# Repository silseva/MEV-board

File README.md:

# MEV board

Design files of the controller board used in the proof-of-concept setup of the [Multiple Emergency Ventilator project](https://mev.deib.polimi.it/).

The board has been designed to be coupled with an STM32F429 discovery board from ST Microelectronics (STM32F429I-DISC1) and serves a double puropose:
* controller for the closed-loop system regulating the bell-jar level;
* controller for the inspiration/expiration valves at bed side.

The design files are released in the Kicad 8.0 format under the [Creative Commons BY-NC-SA 4.0 license](https://creativecommons.org/licenses/by-nc-sa/4.0/).

**DISCLAIMER:** the hardware design made available in this repository has been made for a proof-of-concept setup. Therefore, it must not be considered safe for clinical use.

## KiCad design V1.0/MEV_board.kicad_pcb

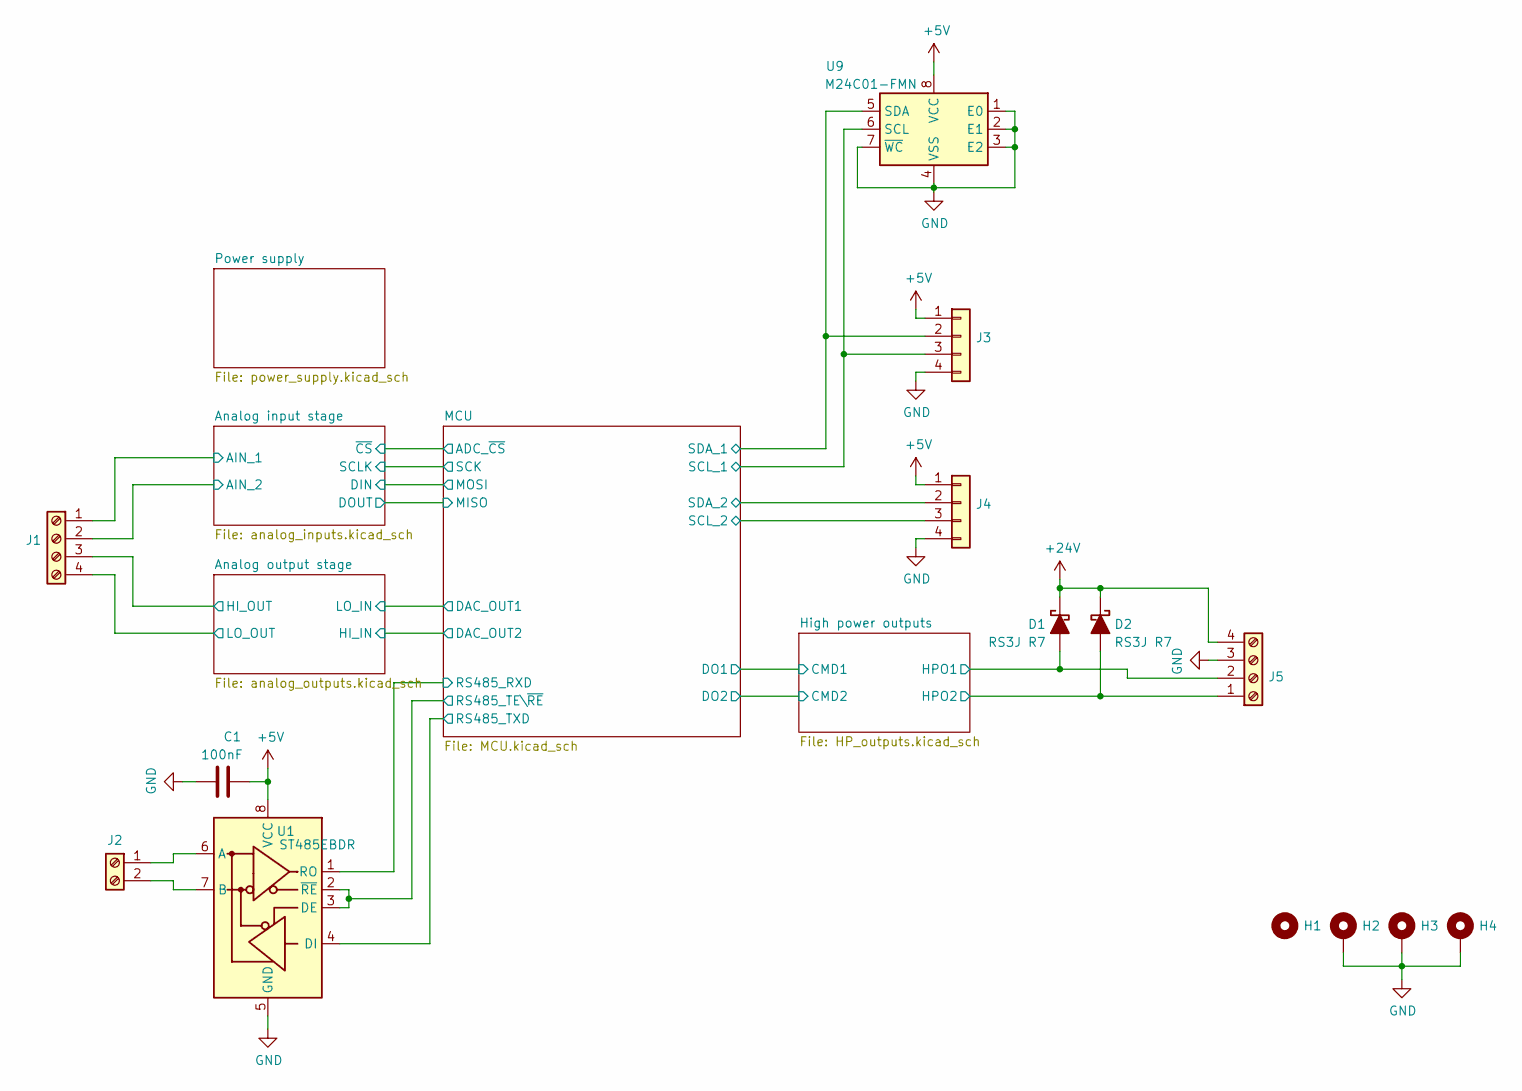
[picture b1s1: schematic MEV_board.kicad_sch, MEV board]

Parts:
C1: 100nF; C_0603_1608Metric_Pad1.08x0.95mm_HandSolder
D1, D2: RS3J R7; D_SMC_Handsoldering
H1, H2, H3, H4: MountingHole_3.2mm_M3_Pad_TopBottom
J1, J5: TerminalBlock_Phoenix_MKDS-1,5-4-5.08_1x04_P5.08mm_Horizont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
J2: TerminalBlock_Phoenix_MKDS-1,5-2-5.08_1x02_P5.08mm_Horizont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
J3, J4: PinHeader_1x04_P2.54mm_Vertical
U1: ST485EBDR; SOIC-8_3.9x4.9mm_P1.27mm
U9: M24C01-FMN; SOIC-8_3.9x4.9mm_P1.27mm

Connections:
+5V: C1.1, J3.1, J4.1, U1.8 (VCC), U9.8 (VCC); also elsewhere on the board
+24V: D1.1 (K), D2.1 (K), J5.4; also elsewhere on the board
/Analog input stage/AIN_1: J1.1; also elsewhere on the board
/Analog input stage/AIN_2: J1.2; also elsewhere on the board
/Analog output stage/HI_OUT: J1.3; also elsewhere on the board
/Analog output stage/LO_OUT: J1.4; also elsewhere on the board
/High power outputs/HPO1: D1.2 (A), J5.2; also elsewhere on the board
/High power outputs/HPO2: D2.2 (A), J5.1; also elsewhere on the board
/MCU/RS485_RXD: U1.1 (RO); also elsewhere on the board
/MCU/RS485_TE\~RE: U1.2 (~RE), U1.3 (DE); also elsewhere on the board
/MCU/RS485_TXD: U1.4 (DI); also elsewhere on the board
/MCU/SCL_1: J3.3, U9.6 (SCL); also elsewhere on the board
/MCU/SCL_2: J4.3; also elsewhere on the board
/MCU/SDA_1: J3.2, U9.5 (SDA); also elsewhere on the board
/MCU/SDA_2: J4.2; also elsewhere on the board
GND: C1.2, H2.1, H3.1, H4.1, J3.4, J4.4, J5.3, U1.5 (GND), U9.1 (E0), U9.2 (E1), U9.3 (E2), U9.4 (VSS), U9.7 (~WC); also elsewhere on the board

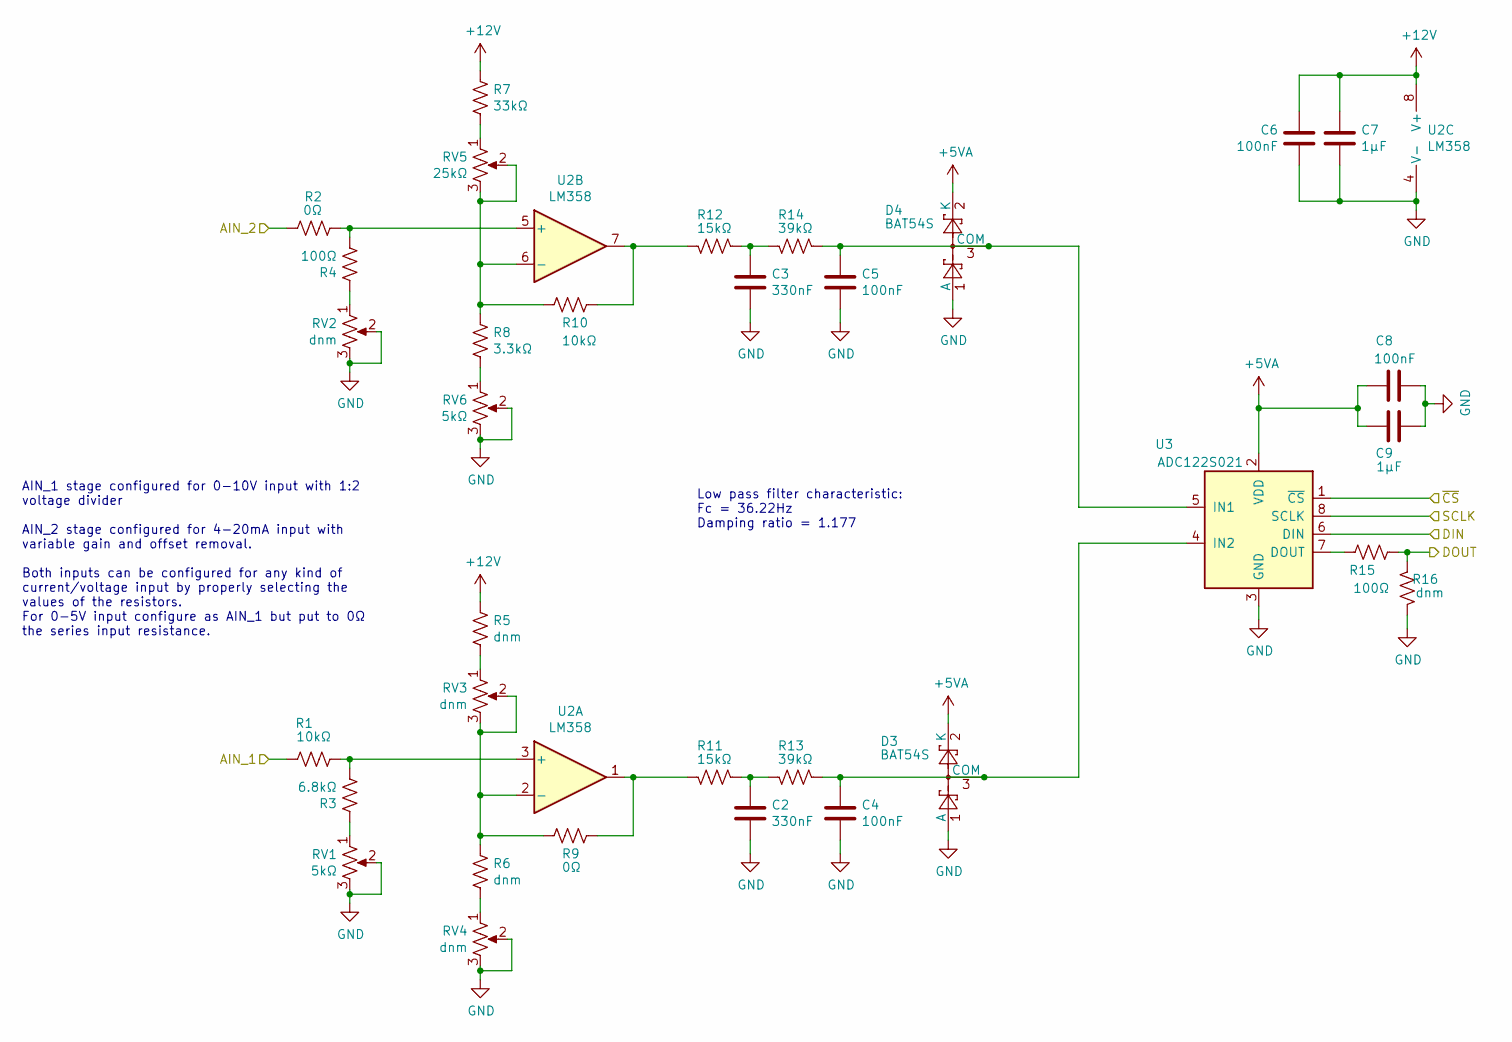
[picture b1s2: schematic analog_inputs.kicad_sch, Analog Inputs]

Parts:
C2, C3: 330nF; C_0805_2012Metric_Pad1.18x1.45mm_HandSolder
C4, C5: 100nF; C_0805_2012Metric_Pad1.18x1.45mm_HandSolder
C6, C8: 100nF; C_0603_1608Metric_Pad1.08x0.95mm_HandSolder
C7, C9: 1μF; C_0603_1608Metric_Pad1.08x0.95mm_HandSolder
D3, D4: BAT54S; SOT-23
R1, R10: 10kΩ; R_0805_2012Metric_Pad1.20x1.40mm_HandSolder
R2, R9: 0Ω; R_0805_2012Metric_Pad1.20x1.40mm_HandSolder
R3: 6.8kΩ; R_0805_2012Metric_Pad1.20x1.40mm_HandSolder
R4: 100Ω; R_0805_2012Metric_Pad1.20x1.40mm_HandSolder
R5, R6, R16: dnm; R_0805_2012Metric_Pad1.20x1.40mm_HandSolder
R7: 33kΩ; R_0805_2012Metric_Pad1.20x1.40mm_HandSolder
R8: 3.3kΩ; R_0805_2012Metric_Pad1.20x1.40mm_HandSolder
R11, R12: 15kΩ; R_0603_1608Metric_Pad0.98x0.95mm_HandSolder
R13, R14: 39kΩ; R_0603_1608Metric_Pad0.98x0.95mm_HandSolder
R15: 100Ω; R_0603_1608Metric_Pad0.98x0.95mm_HandSolder
RV1, RV6: 5kΩ; Potentiometer_Bourns_3296W_Vertical
RV2, RV3, RV4: dnm; Potentiometer_Bourns_3296W_Vertical
RV5: 25kΩ; Potentiometer_Bourns_3296W_Vertical
U2: LM358; SOIC-8_3.9x4.9mm_P1.27mm
U3: ADC122S021; VSSOP-8_3.0x3.0mm_P0.65mm

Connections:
+5VA: C8.1, C9.1, D3.2 (K), D4.2 (K), U3.2 (VDD); also elsewhere on the board
+12V: C6.2, C7.1, R5.1, R7.1, U2.8 (V+); also elsewhere on the board
/Analog input stage/AIN_1: R1.1; also elsewhere on the board
/Analog input stage/AIN_2: R2.1; also elsewhere on the board
/Analog input stage/DIN: U3.6 (DIN); also elsewhere on the board
/Analog input stage/DOUT: R15.2, R16.1; also elsewhere on the board
/MCU/ADC_~CS: U3.1 (~CS); also elsewhere on the board
/MCU/SCK: U3.8 (SCLK); also elsewhere on the board
GND: C2.2, C3.2, C4.2, C5.2, C6.1, C7.2, C8.2, C9.2, D3.1 (A), D4.1 (A), R16.2, RV1.2, RV1.3, RV2.2, RV2.3, RV4.2, RV4.3, RV6.2, RV6.3, U2.4 (V-), U3.3 (GND); also elsewhere on the board
unnamed: C2.1, R11.1, R13.2
unnamed: C3.1, R12.1, R14.2
unnamed: C4.1, D3.3 (COM), R13.1, U3.4 (IN2)
unnamed: C5.1, D4.3 (COM), R14.1, U3.5 (IN1)
unnamed: R1.2, R3.2, U2.3 (+)
unnamed: R2.2, R4.2, U2.5 (+)
unnamed: R3.1, RV1.1
unnamed: R4.1, RV2.1
unnamed: R5.2, RV3.1
unnamed: R6.1, R9.2, RV3.2, RV3.3, U2.2 (-)
unnamed: R6.2, RV4.1
unnamed: R7.2, RV5.1
unnamed: R8.2, RV6.1
unnamed: R10.1, R12.2, U2.7
unnamed: R8.1, R10.2, RV5.2, RV5.3, U2.6 (-)
unnamed: R9.1, R11.2, U2.1
unnamed: R15.1, U3.7 (DOUT)

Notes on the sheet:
AIN_1 stage configured for 0-10V input with 1:2 voltage divider AIN_2 stage configured for 4-20mA input with variable gain and offset removal. Both inputs can be configured for any kind of current/voltage input by properly selecting the values of the resistors. For 0-5V input configure as AIN_1 but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
Low pass filter characteristic: Fc = 36.22Hz Damping ratio = 1.177

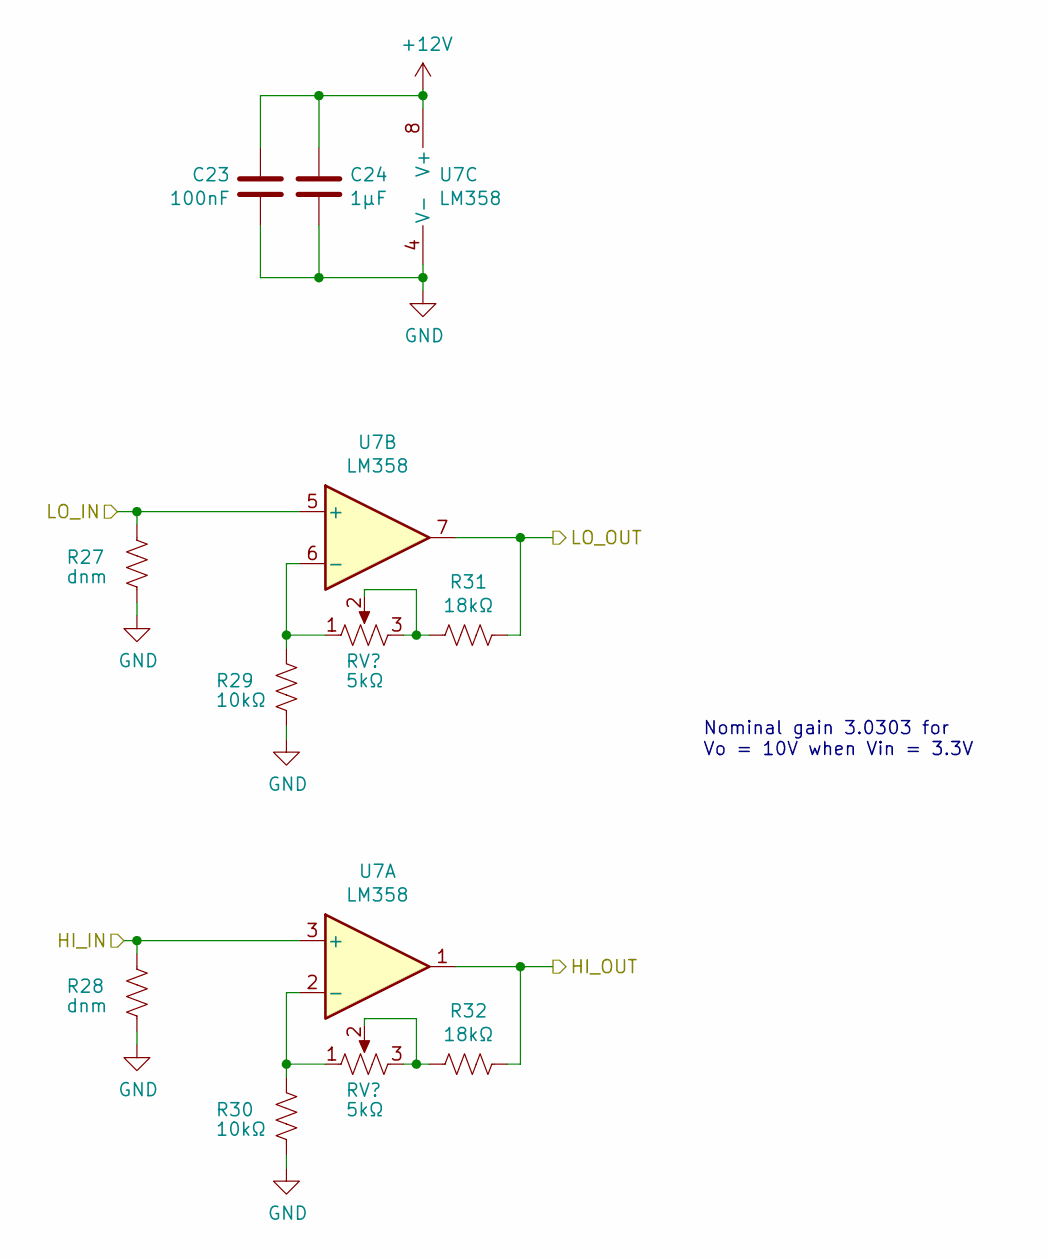
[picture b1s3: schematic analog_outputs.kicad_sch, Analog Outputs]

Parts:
C23: 100nF; C_0603_1608Metric_Pad1.08x0.95mm_HandSolder
C24: 1μF; C_0603_1608Metric_Pad1.08x0.95mm_HandSolder
R27, R28: dnm; R_0805_2012Metric_Pad1.20x1.40mm_HandSolder
R29, R30: 10kΩ; R_0805_2012Metric_Pad1.20x1.40mm_HandSolder
R31, R32: 18kΩ; R_0805_2012Metric_Pad1.20x1.40mm_HandSolder
RV7, RV8: 5kΩ; Potentiometer_Bourns_3296W_Vertical
U7: LM358; SOIC-8_3.9x4.9mm_P1.27mm

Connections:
+12V: C23.2, C24.1, U7.8 (V+); also elsewhere on the board
/Analog output stage/HI_OUT: R32.1, U7.1; also elsewhere on the board
/Analog output stage/LO_OUT: R31.1, U7.7; also elsewhere on the board
/MCU/DAC_OUT1: R27.1, U7.5 (+); also elsewhere on the board
/MCU/DAC_OUT2: R28.1, U7.3 (+); also elsewhere on the board
GND: C23.1, C24.2, R27.2, R28.2, R29.2, R30.2, U7.4 (V-); also elsewhere on the board
unnamed: R29.1, RV7.1, U7.6 (-)
unnamed: R30.1, RV8.1, U7.2 (-)
unnamed: R31.2, RV7.2, RV7.3
unnamed: R32.2, RV8.2, RV8.3

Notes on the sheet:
Nominal gain 3.0303 for Vo = 10V when Vin = 3.3V

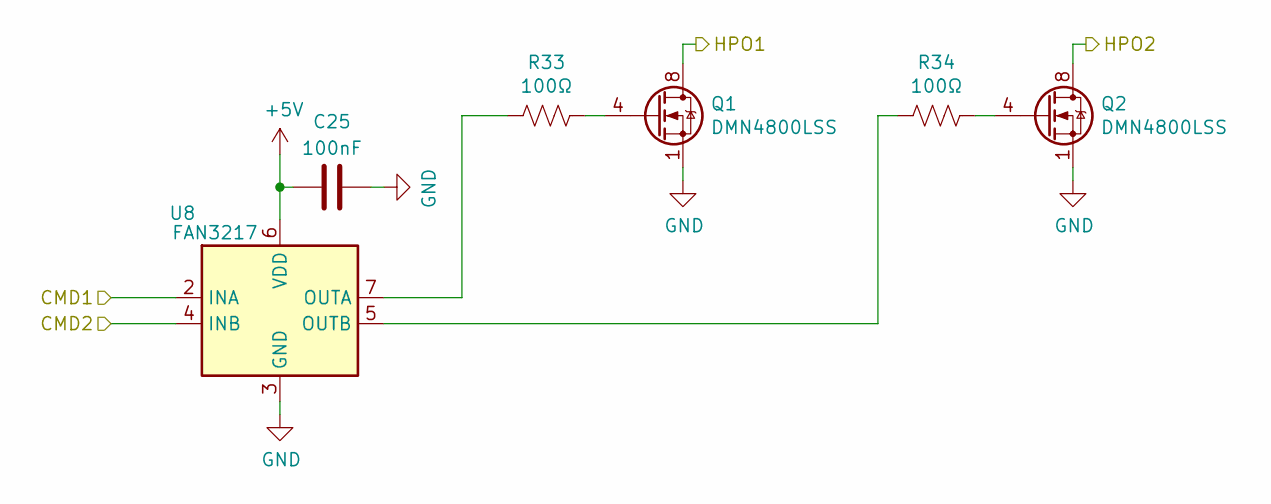
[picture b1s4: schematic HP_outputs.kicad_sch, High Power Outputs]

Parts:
C25: 100nF; C_0603_1608Metric_Pad1.08x0.95mm_HandSolder
Q1, Q2: DMN4800LSS; SOIC-8_3.9x4.9mm_P1.27mm
R33, R34: 100Ω; R_0603_1608Metric_Pad0.98x0.95mm_HandSolder
U8: FAN3217; SOIC-8_3.9x4.9mm_P1.27mm

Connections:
+5V: C25.1, U8.6 (VDD); also elsewhere on the board
/High power outputs/CMD1: U8.2 (INA); also elsewhere on the board
/High power outputs/CMD2: U8.4 (INB); also elsewhere on the board
/High power outputs/HPO1: Q1.5 (D), Q1.6 (D), Q1.7 (D), Q1.8 (D); also elsewhere on the board
/High power outputs/HPO2: Q2.5 (D), Q2.6 (D), Q2.7 (D), Q2.8 (D); also elsewhere on the board
GND: C25.2, Q1.1 (S), Q1.2 (S), Q1.3 (S), Q2.1 (S), Q2.2 (S), Q2.3 (S), U8.3 (GND); also elsewhere on the board
unnamed: Q1.4 (G), R33.1
unnamed: Q2.4 (G), R34.1
unnamed: R33.2, U8.7 (OUTA)
unnamed: R34.2, U8.5 (OUTB)

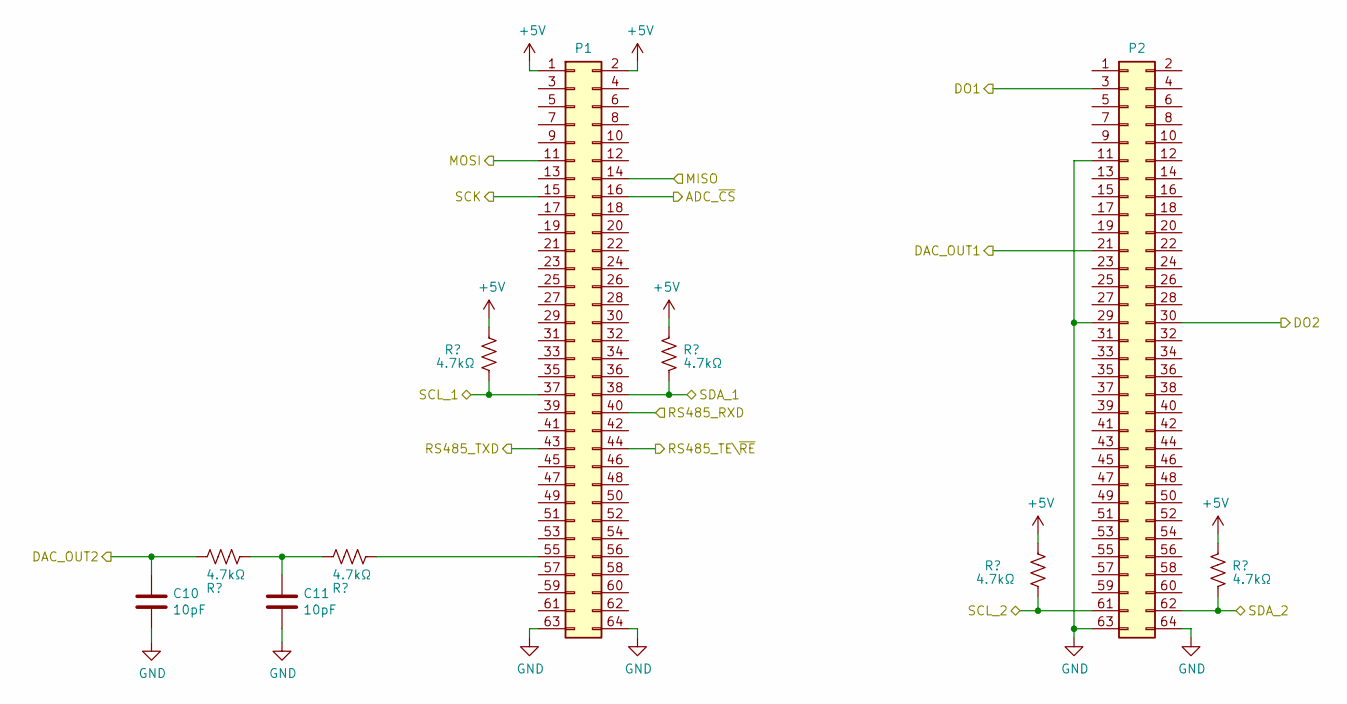
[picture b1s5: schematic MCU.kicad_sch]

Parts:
C10, C11: 10pF; C_0805_2012Metric_Pad1.18x1.45mm_HandSolder
P1, P2: PinHeader_2x32_P2.54mm_Vertical
R17, R18, R19, R22, R23, R26: 4.7kΩ; R_0603_1608Metric_Pad0.98x0.95mm_HandSolder

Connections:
+5V: P1.1, P1.2, R19.2, R22.2, R23.2, R26.2; also elsewhere on the board
/Analog input stage/DIN: P1.11; also elsewhere on the board
/Analog input stage/DOUT: P1.14; also elsewhere on the board
/High power outputs/CMD1: P2.3; also elsewhere on the board
/High power outputs/CMD2: P2.30; also elsewhere on the board
/MCU/ADC_~CS: P1.16; also elsewhere on the board
/MCU/DAC_OUT1: P2.21; also elsewhere on the board
/MCU/DAC_OUT2: C10.1, R17.2; also elsewhere on the board
/MCU/RS485_RXD: P1.40; also elsewhere on the board
/MCU/RS485_TE\~RE: P1.44; also elsewhere on the board
/MCU/RS485_TXD: P1.43; also elsewhere on the board
/MCU/SCK: P1.15; also elsewhere on the board
/MCU/SCL_1: P1.37, R19.1; also elsewhere on the board
/MCU/SCL_2: P2.61, R23.1; also elsewhere on the board
/MCU/SDA_1: P1.38, R22.1; also elsewhere on the board
/MCU/SDA_2: P2.62, R26.1; also elsewhere on the board
GND: C10.2, C11.2, P1.63, P1.64, P2.11, P2.29, P2.63, P2.64; also elsewhere on the board
unnamed: C11.1, R17.1, R18.2
unnamed: P1.55, R18.1

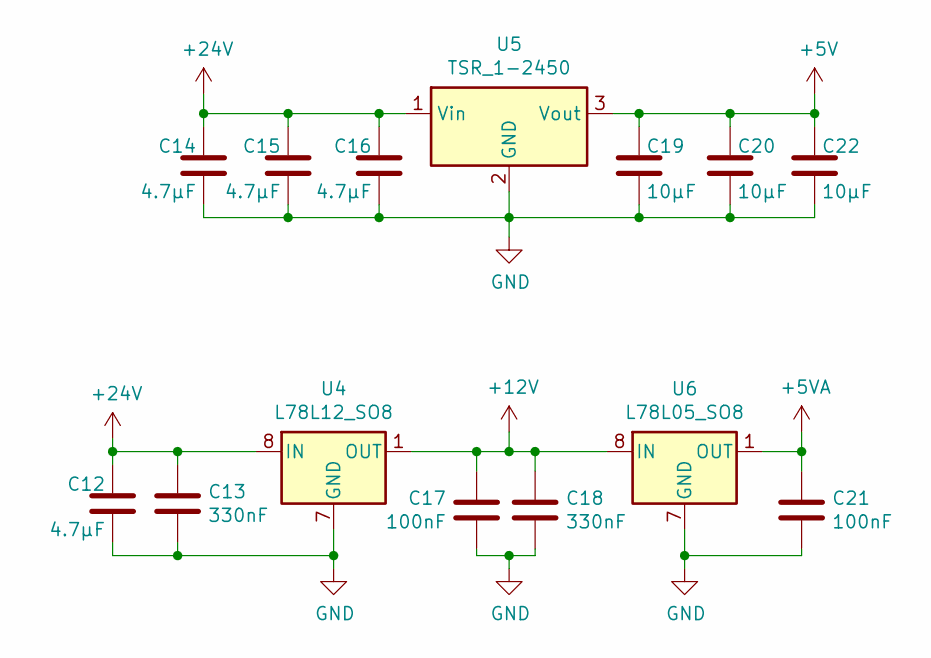
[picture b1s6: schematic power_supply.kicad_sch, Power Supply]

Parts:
C12, C14, C15, C16: 4.7μF; C_0805_2012Metric_Pad1.18x1.45mm_HandSolder
C13, C18: 330nF; C_0805_2012Metric_Pad1.18x1.45mm_HandSolder
C17, C21: 100nF; C_0603_1608Metric_Pad1.08x0.95mm_HandSolder
C19, C20, C22: 10μF; C_0805_2012Metric_Pad1.18x1.45mm_HandSolder
U4: L78L12_SO8; SOIC-8_3.9x4.9mm_P1.27mm
U5: TSR_1-2450; Converter_DCDC_TRACO_TSR-1_THT
U6: L78L05_SO8; SOIC-8_3.9x4.9mm_P1.27mm

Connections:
+5V: C19.2, C20.2, C22.2, U5.3 (Vout); also elsewhere on the board
+5VA: C21.2, U6.1 (OUT); also elsewhere on the board
+12V: C17.2, C18.2, U4.1 (OUT), U6.8 (IN); also elsewhere on the board
+24V: C12.2, C13.2, C14.2, C15.2, C16.2, U4.8 (IN), U5.1 (Vin); also elsewhere on the board
GND: C12.1, C13.1, C14.1, C15.1, C16.1, C17.1, C18.1, C19.1, C20.1, C21.1, C22.1, U4.2 (GND), U4.3 (GND), U4.6 (GND), U4.7 (GND), U5.2 (GND), U6.2 (GND), U6.3 (GND), U6.6 (GND), U6.7 (GND); also elsewhere on the board

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
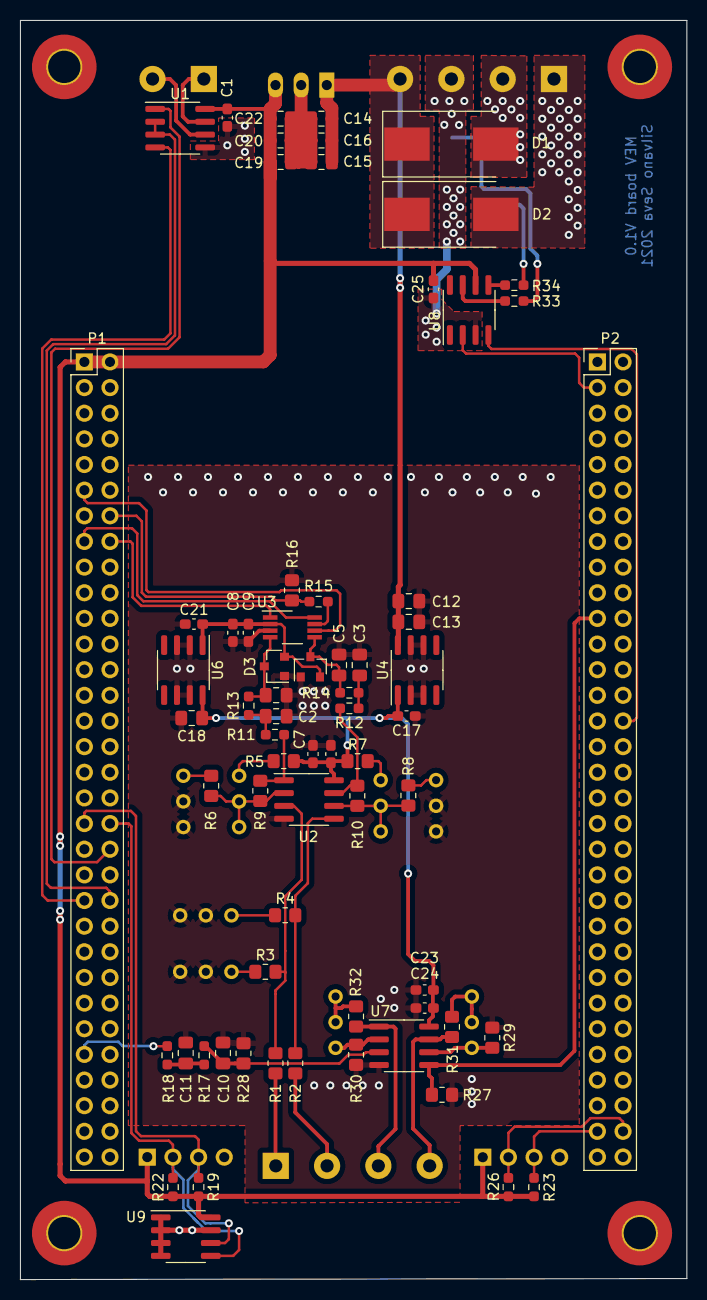
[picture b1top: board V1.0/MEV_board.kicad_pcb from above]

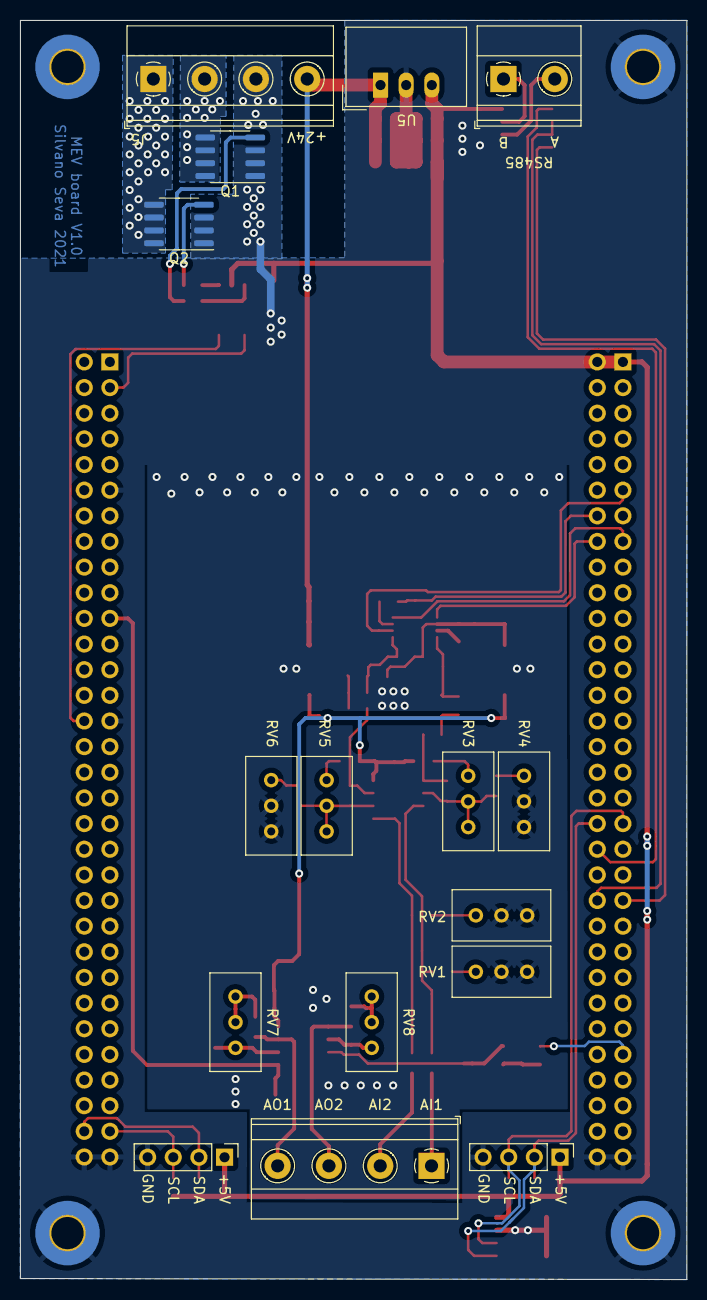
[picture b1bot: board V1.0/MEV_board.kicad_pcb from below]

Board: 2 copper layers, 66.0 x 124.7 mm, 89 parts (16 on the bottom side), 55 nets.

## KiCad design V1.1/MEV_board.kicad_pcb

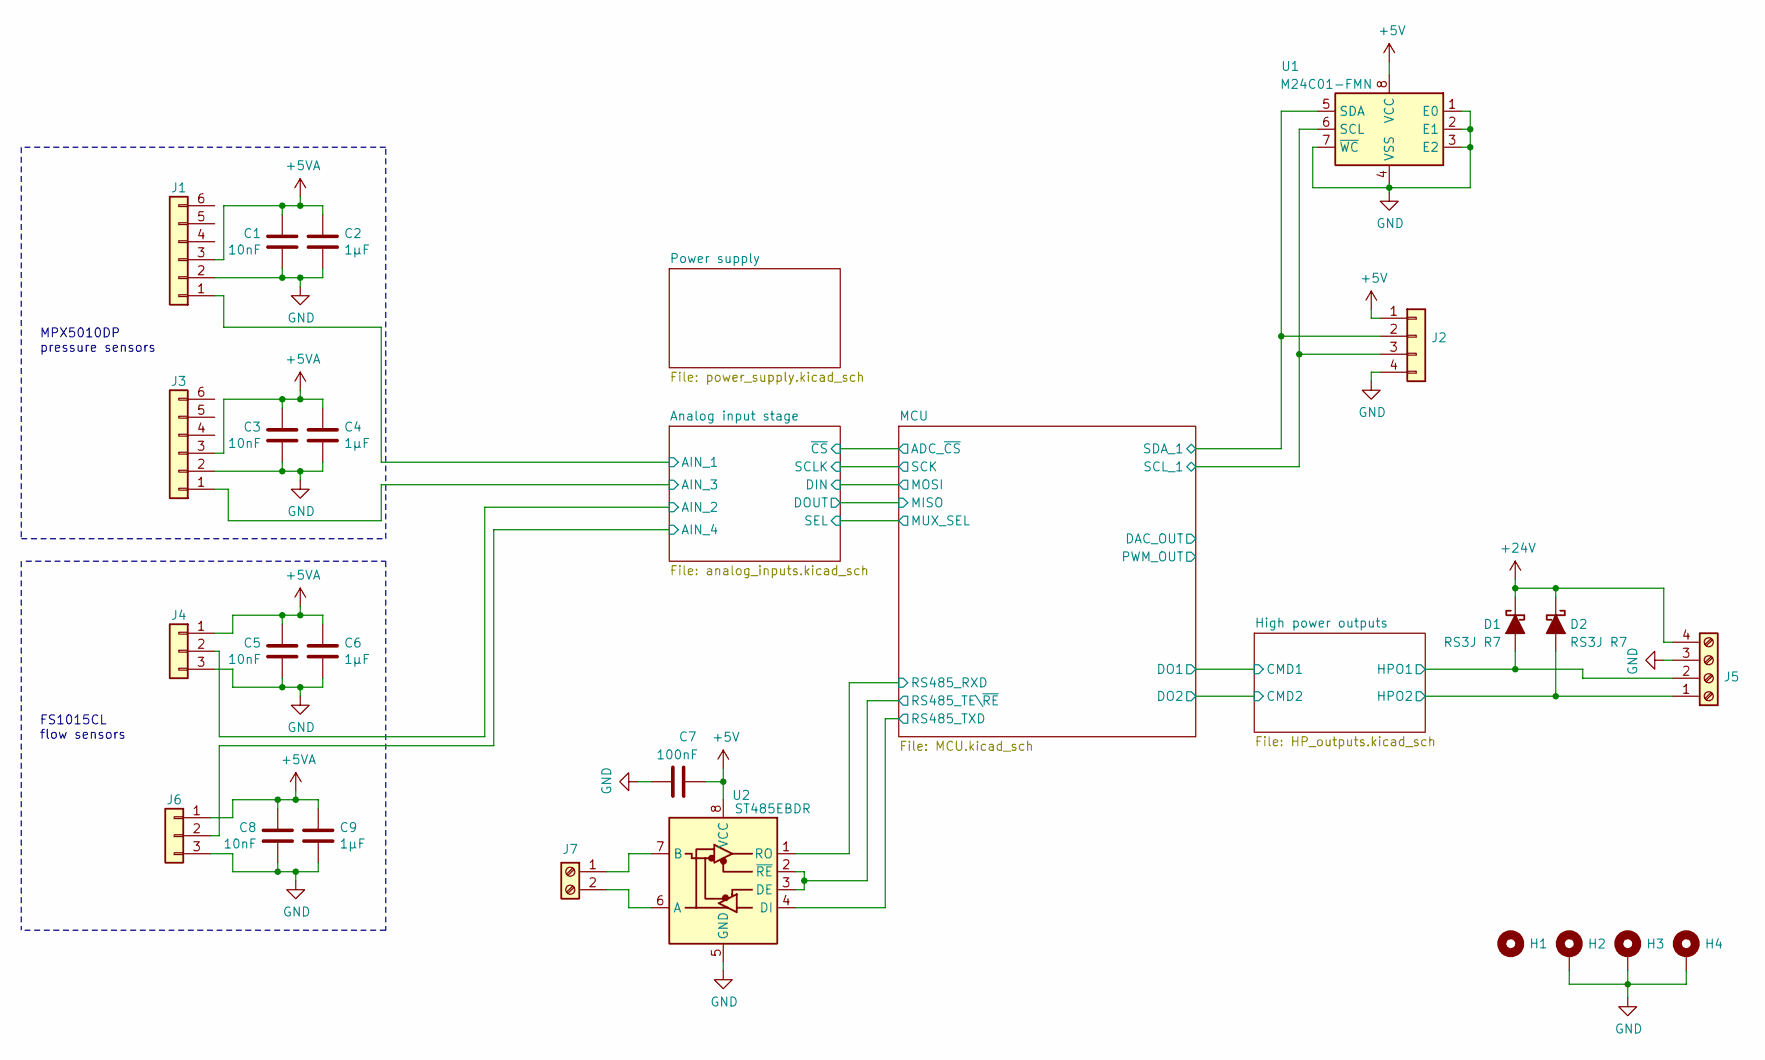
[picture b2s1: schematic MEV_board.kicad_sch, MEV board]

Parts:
C1, C3, C5, C8: 10nF; C_0603_1608Metric_Pad1.08x0.95mm_HandSolder
C2, C4, C6, C9: 1μF; C_0603_1608Metric_Pad1.08x0.95mm_HandSolder
C7: 100nF; C_0603_1608Metric_Pad1.08x0.95mm_HandSolder
D1, D2: RS3J R7; D_SMC_Handsoldering
H1, H2, H3, H4: MountingHole_3.2mm_M3_Pad_TopBottom
J1, J3: PinSocket_1x06_P2.54mm_Vertical
J2: PinHeader_1x04_P2.54mm_Vertical
J4, J6: Molex_KK-254_AE-6410-03A_1x03_P2.54mm_Vertical
J5: TerminalBlock_Phoenix_MKDS-1,5-4-5.08_1x04_P5.08mm_Horizont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
J7: TerminalBlock_Phoenix_MKDS-1,5-2-5.08_1x02_P5.08mm_Horizont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
U1: M24C01-FMN; SOIC-8_3.9x4.9mm_P1.27mm
U2: ST485EBDR; SOIC-8_3.9x4.9mm_P1.27mm

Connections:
+5V: C7.1, J2.1, U1.8 (VCC), U2.8 (VCC); also elsewhere on the board
+5VA: C1.2, C2.1, C3.2, C4.1, C5.2, C6.1, C8.2, C9.1, J1.3, J3.3, J4.1, J6.1; also elsewhere on the board
+24V: D1.1 (K), D2.1 (K), J5.4; also elsewhere on the board
/Analog input stage/AIN_1: J1.1; also elsewhere on the board
/Analog input stage/AIN_2: J4.2; also elsewhere on the board
/Analog input stage/AIN_3: J3.1; also elsewhere on the board
/Analog input stage/AIN_4: J6.2; also elsewhere on the board
/High power outputs/HPO1: D1.2 (A), J5.2; also elsewhere on the board
/High power outputs/HPO2: D2.2 (A), J5.1; also elsewhere on the board
/MCU/RS485_RXD: U2.1 (RO); also elsewhere on the board
/MCU/RS485_TE\~RE: U2.2 (~RE), U2.3 (DE); also elsewhere on the board
/MCU/RS485_TXD: U2.4 (DI); also elsewhere on the board
/MCU/SCL_1: J2.3, U1.6 (SCL); also elsewhere on the board
/MCU/SDA_1: J2.2, U1.5 (SDA); also elsewhere on the board
GND: C1.1, C2.2, C3.1, C4.2, C5.1, C6.2, C7.2, C8.1, C9.2, H2.1, H3.1, H4.1, J1.2, J2.4, J3.2, J4.3, J5.3, J6.3, U1.1 (E0), U1.2 (E1), U1.3 (E2), U1.4 (VSS), U1.7 (~WC), U2.5 (GND); also elsewhere on the board
unnamed: J7.1, U2.7 (B)
unnamed: J7.2, U2.6 (A)

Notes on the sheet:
FS1015CL flow sensors
MPX5010DP pressure sensors

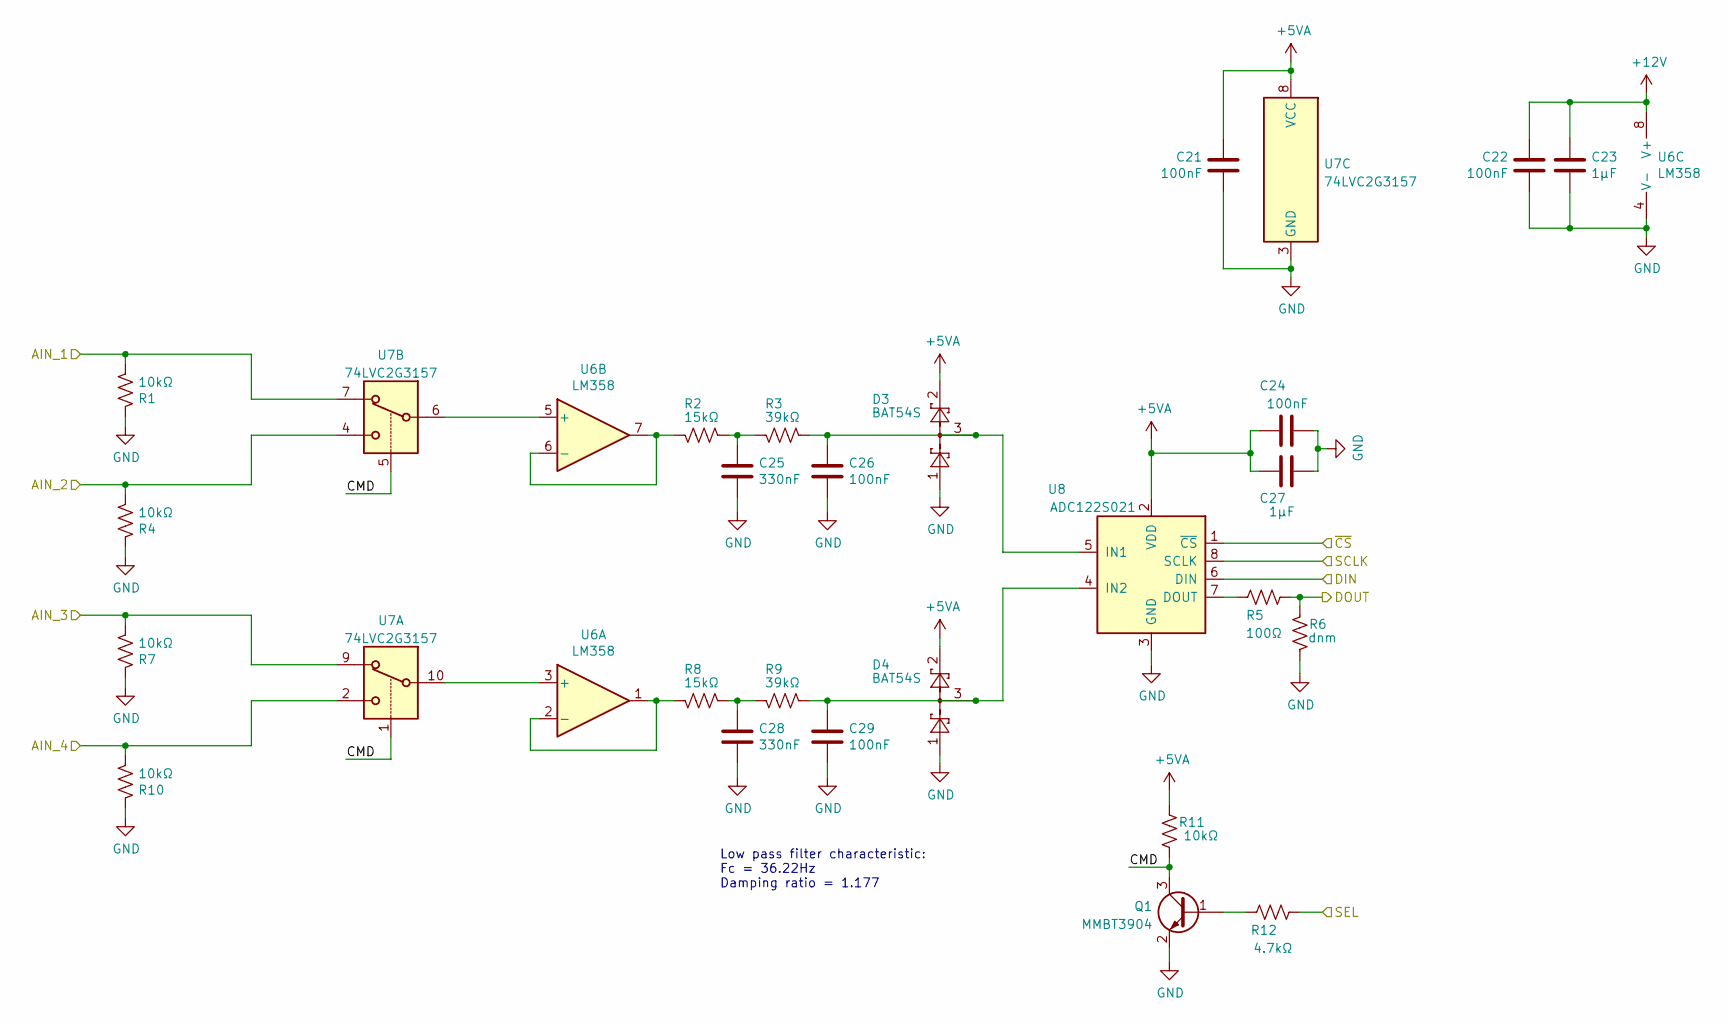
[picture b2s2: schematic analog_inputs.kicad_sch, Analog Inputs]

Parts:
C21, C22, C24, C26, C29: 100nF; C_0603_1608Metric_Pad1.08x0.95mm_HandSolder
C23, C27: 1μF; C_0603_1608Metric_Pad1.08x0.95mm_HandSolder
C25, C28: 330nF; C_0805_2012Metric_Pad1.18x1.45mm_HandSolder
D3, D4: BAT54S; SOT-23
Q1: MMBT3904; SOT-23
R1, R4, R7, R10, R11: 10kΩ; R_0805_2012Metric_Pad1.20x1.40mm_HandSolder
R2, R8: 15kΩ; R_0603_1608Metric_Pad0.98x0.95mm_HandSolder
R3, R9: 39kΩ; R_0603_1608Metric_Pad0.98x0.95mm_HandSolder
R5: 100Ω; R_0603_1608Metric_Pad0.98x0.95mm_HandSolder
R6: dnm; R_0805_2012Metric_Pad1.20x1.40mm_HandSolder
R12: 4.7kΩ; R_0603_1608Metric_Pad0.98x0.95mm_HandSolder
U6: LM358; SOIC-8_3.9x4.9mm_P1.27mm
U7: 74LVC2G3157; TSSOP-10_3x3mm_P0.5mm
U8: ADC122S021; VSSOP-8_3.0x3.0mm_P0.65mm

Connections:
+5VA: C21.2, C24.1, C27.1, D3.2, D4.2, R11.2, U7.8 (VCC), U8.2 (VDD); also elsewhere on the board
+12V: C22.2, C23.1, U6.8 (V+); also elsewhere on the board
/Analog input stage/AIN_1: R1.2, U7.7; also elsewhere on the board
/Analog input stage/AIN_2: R4.2, U7.4; also elsewhere on the board
/Analog input stage/AIN_3: R7.2, U7.9; also elsewhere on the board
/Analog input stage/AIN_4: R10.2, U7.2; also elsewhere on the board
/Analog input stage/CMD: Q1.3 (C), R11.1, U7.1, U7.5
/Analog input stage/DIN: U8.6 (DIN); also elsewhere on the board
/Analog input stage/DOUT: R5.2, R6.1; also elsewhere on the board
/Analog input stage/SCLK: U8.8 (SCLK); also elsewhere on the board
/Analog input stage/SEL: R12.2; also elsewhere on the board
/Analog input stage/~CS: U8.1 (~CS); also elsewhere on the board
GND: C21.1, C22.1, C23.2, C24.2, C25.2, C26.2, C27.2, C28.2, C29.2, D3.1, D4.1, Q1.2 (E), R1.1, R4.1, R6.2, R7.1, R10.1, U6.4 (V-), U7.3 (GND), U8.3 (GND); also elsewhere on the board
unnamed: C25.1, R2.1, R3.2
unnamed: C26.1, D3.3, R3.1, U8.5 (IN1)
unnamed: C28.1, R8.1, R9.2
unnamed: C29.1, D4.3, R9.1, U8.4 (IN2)
unnamed: Q1.1 (B), R12.1
unnamed: R2.2, U6.6 (-), U6.7
unnamed: R5.1, U8.7 (DOUT)
unnamed: R8.2, U6.1, U6.2 (-)
unnamed: U6.3 (+), U7.10
unnamed: U6.5 (+), U7.6

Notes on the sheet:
Low pass filter characteristic: Fc = 36.22Hz Damping ratio = 1.177

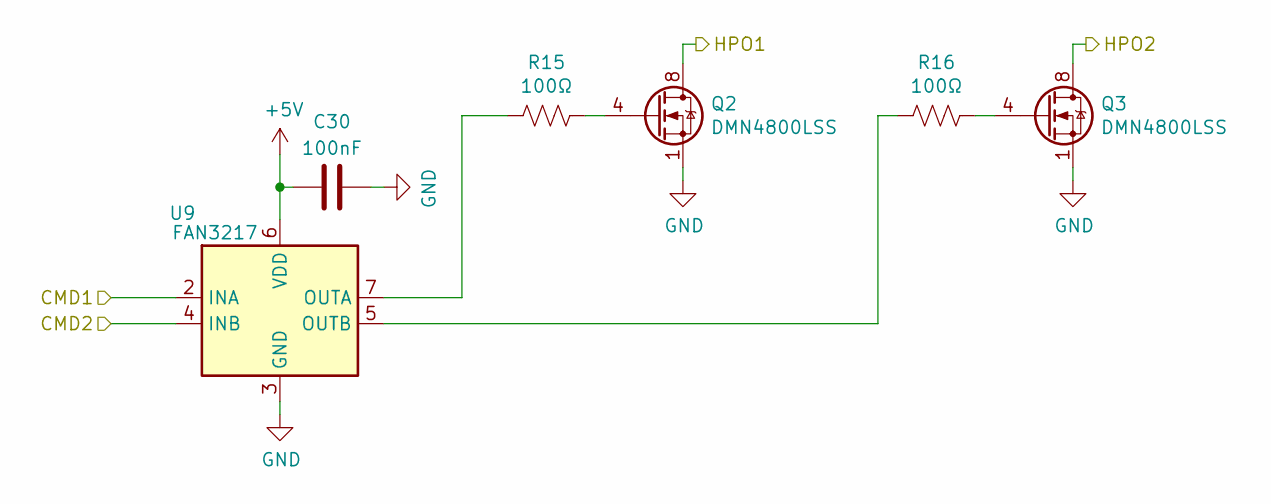
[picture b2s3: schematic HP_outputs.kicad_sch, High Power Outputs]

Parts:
C30: 100nF; C_0603_1608Metric_Pad1.08x0.95mm_HandSolder
Q2, Q3: DMN4800LSS; SOIC-8_3.9x4.9mm_P1.27mm
R15, R16: 100Ω; R_0603_1608Metric_Pad0.98x0.95mm_HandSolder
U9: FAN3217; SOIC-8_3.9x4.9mm_P1.27mm

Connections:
+5V: C30.1, U9.6 (VDD); also elsewhere on the board
/High power outputs/CMD1: U9.2 (INA); also elsewhere on the board
/High power outputs/CMD2: U9.4 (INB); also elsewhere on the board
/High power outputs/HPO1: Q2.5 (D), Q2.6 (D), Q2.7 (D), Q2.8 (D); also elsewhere on the board
/High power outputs/HPO2: Q3.5 (D), Q3.6 (D), Q3.7 (D), Q3.8 (D); also elsewhere on the board
GND: C30.2, Q2.1 (S), Q2.2 (S), Q2.3 (S), Q3.1 (S), Q3.2 (S), Q3.3 (S), U9.3 (GND); also elsewhere on the board
unnamed: Q2.4 (G), R15.1
unnamed: Q3.4 (G), R16.1
unnamed: R15.2, U9.7 (OUTA)
unnamed: R16.2, U9.5 (OUTB)

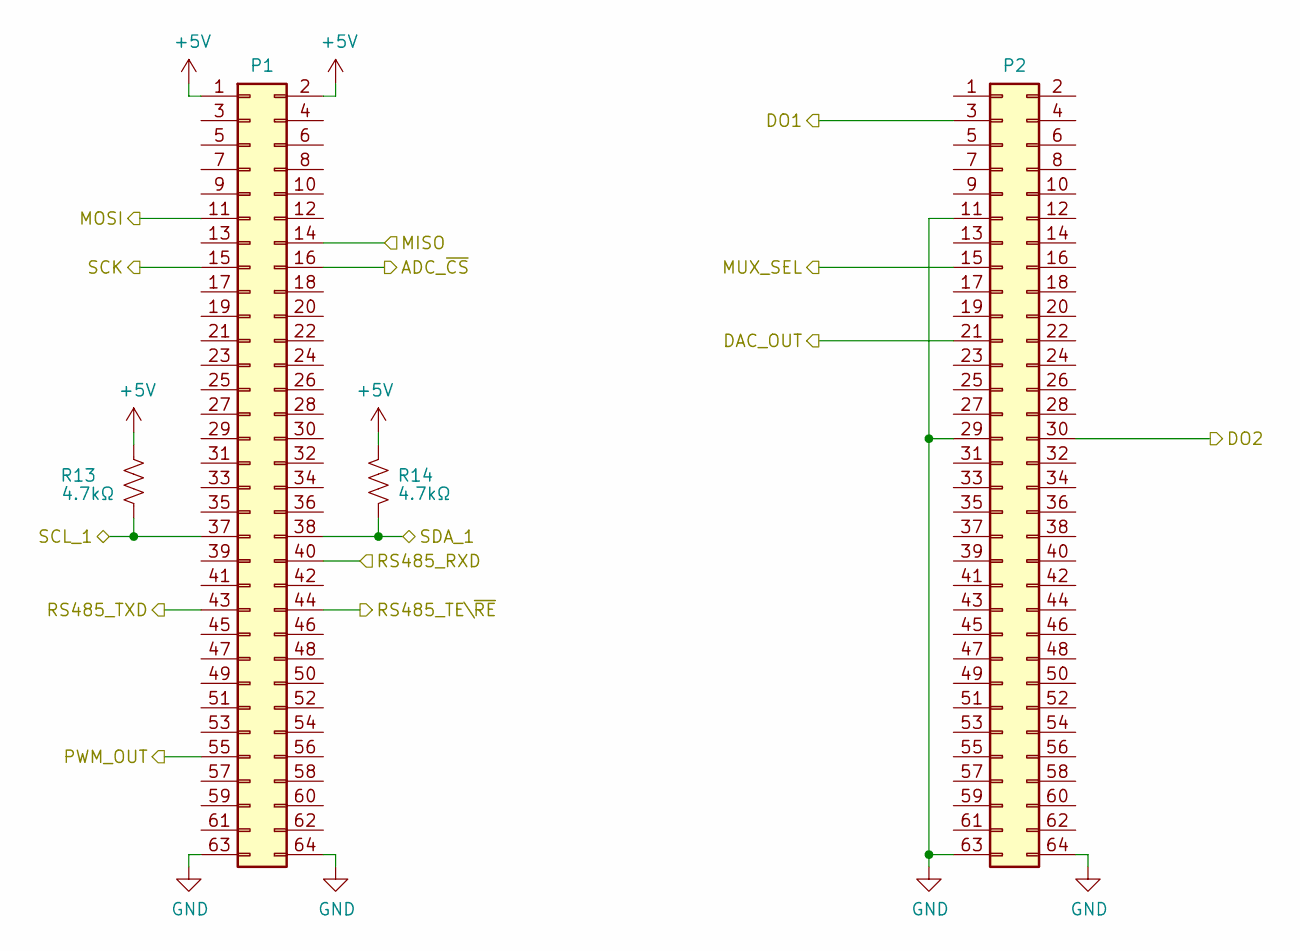
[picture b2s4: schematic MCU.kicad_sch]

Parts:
P1, P2: PinHeader_2x32_P2.54mm_Vertical
R13, R14: 4.7kΩ; R_0603_1608Metric_Pad0.98x0.95mm_HandSolder

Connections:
+5V: P1.1, P1.2, R13.2, R14.2; also elsewhere on the board
/Analog input stage/DIN: P1.11; also elsewhere on the board
/Analog input stage/DOUT: P1.14; also elsewhere on the board
/Analog input stage/SCLK: P1.15; also elsewhere on the board
/Analog input stage/SEL: P2.15; also elsewhere on the board
/Analog input stage/~CS: P1.16; also elsewhere on the board
/High power outputs/CMD1: P2.3; also elsewhere on the board
/High power outputs/CMD2: P2.30; also elsewhere on the board
/MCU/DAC_OUT: P2.21
/MCU/PWM_OUT: P1.55
/MCU/RS485_RXD: P1.40; also elsewhere on the board
/MCU/RS485_TE\~RE: P1.44; also elsewhere on the board
/MCU/RS485_TXD: P1.43; also elsewhere on the board
/MCU/SCL_1: P1.37, R13.1; also elsewhere on the board
/MCU/SDA_1: P1.38, R14.1; also elsewhere on the board
GND: P1.63, P1.64, P2.11, P2.29, P2.63, P2.64; also elsewhere on the board

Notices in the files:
V1.0/HP_outputs.kicad_sch:
Released under CC BY-NC-SA license
